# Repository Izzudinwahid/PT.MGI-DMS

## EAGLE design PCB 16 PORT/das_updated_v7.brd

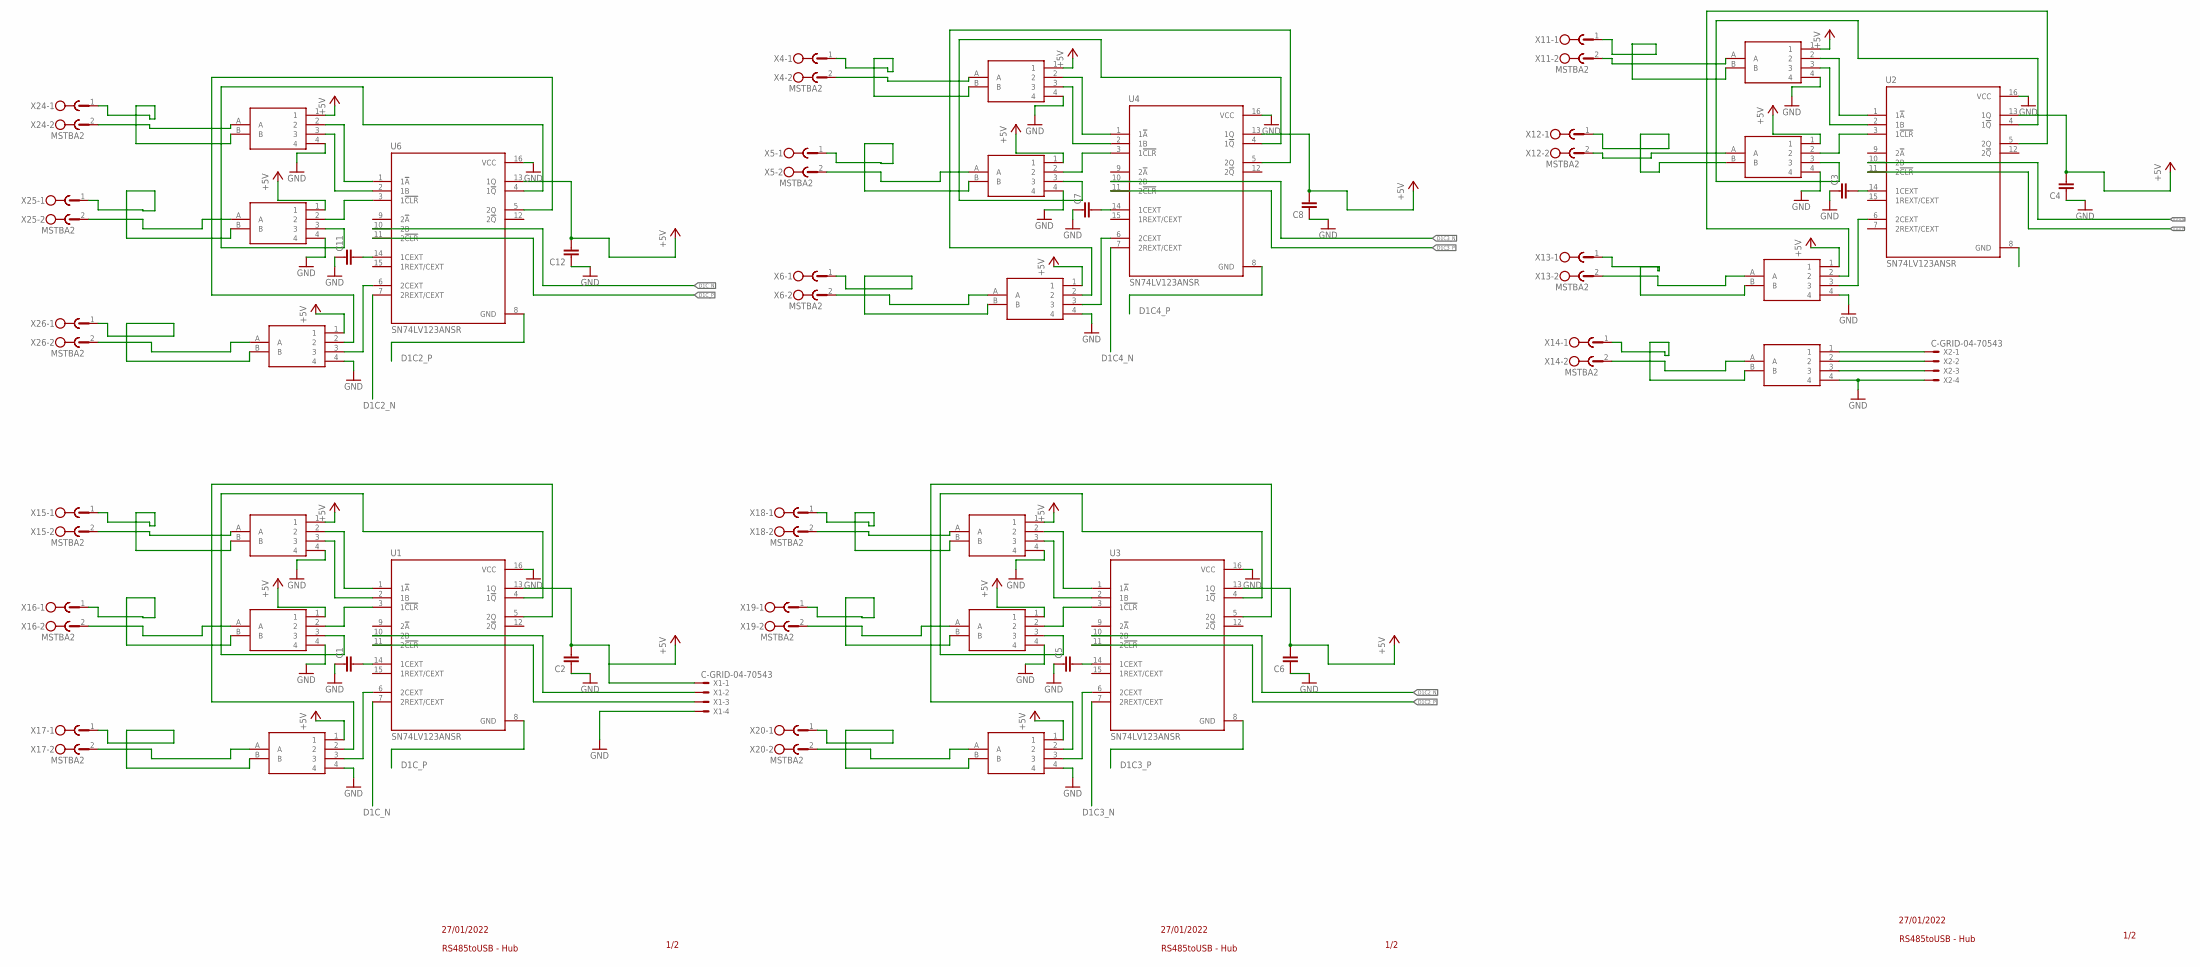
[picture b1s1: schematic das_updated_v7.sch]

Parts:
C1, C2, C3, C4, C5, C6, C7, C8, C11, C12: C-EUC0603K; C0603K
U1, U2, U3, U4, U6: SN74LV123ANSR; SOIC127P780X200-16N
USB2RS1, USB2RS2, USB2RS3, USB2RS4, USB2RS5, USB2RS6, USB2RS7, USB2RS8, USB2RS9, USB2RS10, USB2RS11, USB2RS12, USB2RS13, USB2RS17, USB2RS18, USB2RS19: USB2RS485
X1, X2: C-GRID-04-70543; 70543-04
X4, X5, X6, X11, X12, X13, X14, X15, X16, X17, X18, X19, X20, X24, X25, X26: MSTBA2

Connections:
+5V: C2.2, C4.2, C6.2, C8.2, C12.2, U1.13 (1Q), U2.13 (1Q), U3.13 (1Q), U4.13 (1Q), U6.13 (1Q), USB2RS1.1, USB2RS2.1, USB2RS3.1, USB2RS4.1, USB2RS5.1, USB2RS6.1, USB2RS7.1, USB2RS9.1, USB2RS10.1, USB2RS11.1, USB2RS12.1, USB2RS13.1, USB2RS17.1, USB2RS18.1, USB2RS19.1, X1.1
D1C2_N: U3.10 (2B), U6.7 (2REXT/CEXT)
D1C2_P: U3.11 (2!CLR), U6.8 (GND)
D1C3_N: U3.7 (2REXT/CEXT), U4.10 (2B)
D1C3_P: U3.8 (GND), U4.11 (2!CLR)
D1C4_N: U2.10 (2B), U4.7 (2REXT/CEXT)
D1C4_P: U2.11 (2!CLR), U4.8 (GND)
D1C_N: U1.7 (2REXT/CEXT), U6.10 (2B)
D1C_P: U1.8 (GND), U6.11 (2!CLR)
D2-: USB2RS8.2, X2.2
D_N: U1.11 (2!CLR), X1.3
D_P: U1.10 (2B), X1.2
GND: C1.1, C2.1, C3.1, C4.1, C5.1, C6.1, C7.1, C8.1, C11.1, C12.1, U1.16 (VCC), U2.16 (VCC), U3.16 (VCC), U4.16 (VCC), U6.16 (VCC), USB2RS1.4, USB2RS2.4, USB2RS3.4, USB2RS4.4, USB2RS5.4, USB2RS6.4, USB2RS7.4, USB2RS8.4, USB2RS9.4, USB2RS10.4, USB2RS11.4, USB2RS12.4, USB2RS13.4, USB2RS17.4, USB2RS18.4, USB2RS19.4, X1.4, X2.4
MOD2_N: U1.6 (2CEXT), USB2RS3.3
MOD2_N1: U3.6 (2CEXT), USB2RS10.3
MOD2_N2: U4.6 (2CEXT), USB2RS13.3
MOD2_N4: U6.6 (2CEXT), USB2RS19.3
MOD2_P: U1.5 (2Q), USB2RS3.2
MOD2_P1: U3.5 (2Q), USB2RS10.2
MOD2_P2: U4.5 (2Q), USB2RS13.2
MOD2_P4: U6.5 (2Q), USB2RS19.2
MOD3_N: U1.4 (1!Q), USB2RS2.3
MOD3_N1: U3.4 (1!Q), USB2RS9.3
MOD3_N2: U4.4 (1!Q), USB2RS12.3
MOD3_N4: U6.4 (1!Q), USB2RS18.3
MOD3_P: U1.3 (1!CLR), USB2RS2.2
MOD3_P1: U3.3 (1!CLR), USB2RS9.2
MOD3_P2: U4.3 (1!CLR), USB2RS12.2
MOD3_P4: U6.3 (1!CLR), USB2RS18.2
MOD4_N: U1.2 (1B), USB2RS1.3
MOD4_N1: U3.2 (1B), USB2RS4.3
MOD4_N2: U4.2 (1B), USB2RS11.3
MOD4_N4: U6.2 (1B), USB2RS17.3
MOD4_P: U1.1 (1!A), USB2RS1.2
MOD4_P1: U3.1 (1!A), USB2RS4.2
MOD4_P2: U4.1 (1!A), USB2RS11.2
MOD4_P4: U6.1 (1!A), USB2RS17.2
MOD7_N: U2.6 (2CEXT), USB2RS7.3
MOD7_P: U2.5 (2Q), USB2RS7.2
MOD8_N: U2.4 (1!Q), USB2RS6.3
MOD8_P: U2.3 (1!CLR), USB2RS6.2
MOD9_N: U2.2 (1B), USB2RS5.3
MOD9_P: U2.1 (1!A), USB2RS5.2
unnamed: C5.2, U3.14 (1CEXT)
unnamed: C7.2, U4.14 (1CEXT)
unnamed: USB2RS8.3, X2.3
unnamed: C11.2, U6.14 (1CEXT)
unnamed: C1.2, U1.14 (1CEXT)
unnamed: USB2RS8.1, X2.1
unnamed: C3.2, U2.14 (1CEXT)
X2_N: USB2RS3.B, X17.1
X2_N1: USB2RS10.B, X20.1
X2_N2: USB2RS13.B, X6.1
X2_N4: USB2RS19.B, X26.1
X2_P: USB2RS3.A, X17.2
X2_P1: USB2RS10.A, X20.2
X2_P2: USB2RS13.A, X6.2
X2_P4: USB2RS19.A, X26.2
X3_N: USB2RS2.B, X16.1
X3_N1: USB2RS9.B, X19.1
X3_N2: USB2RS12.B, X5.1
X3_N4: USB2RS18.B, X25.1
X3_P: USB2RS2.A, X16.2
X3_P1: USB2RS9.A, X19.2
X3_P2: USB2RS12.A, X5.2
X3_P4: USB2RS18.A, X25.2
X4_N: USB2RS1.B, X15.1
X4_N1: USB2RS4.B, X18.1
X4_N2: USB2RS11.B, X4.1
X4_N4: USB2RS17.B, X24.1
X4_P: USB2RS1.A, X15.2
X4_P1: USB2RS4.A, X18.2
X4_P2: USB2RS11.A, X4.2
X4_P4: USB2RS17.A, X24.2
X5_N: USB2RS8.B, X14.1
X5_P: USB2RS8.A, X14.2
X6_N: USB2RS7.B, X13.1
X6_P: USB2RS7.A, X13.2
X7_N: USB2RS6.B, X12.1
X7_P: USB2RS6.A, X12.2
X8_N: USB2RS5.B, X11.1
X8_P: USB2RS5.A, X11.2

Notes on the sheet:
27/01/2022
RS485toUSB - Hub
1/2

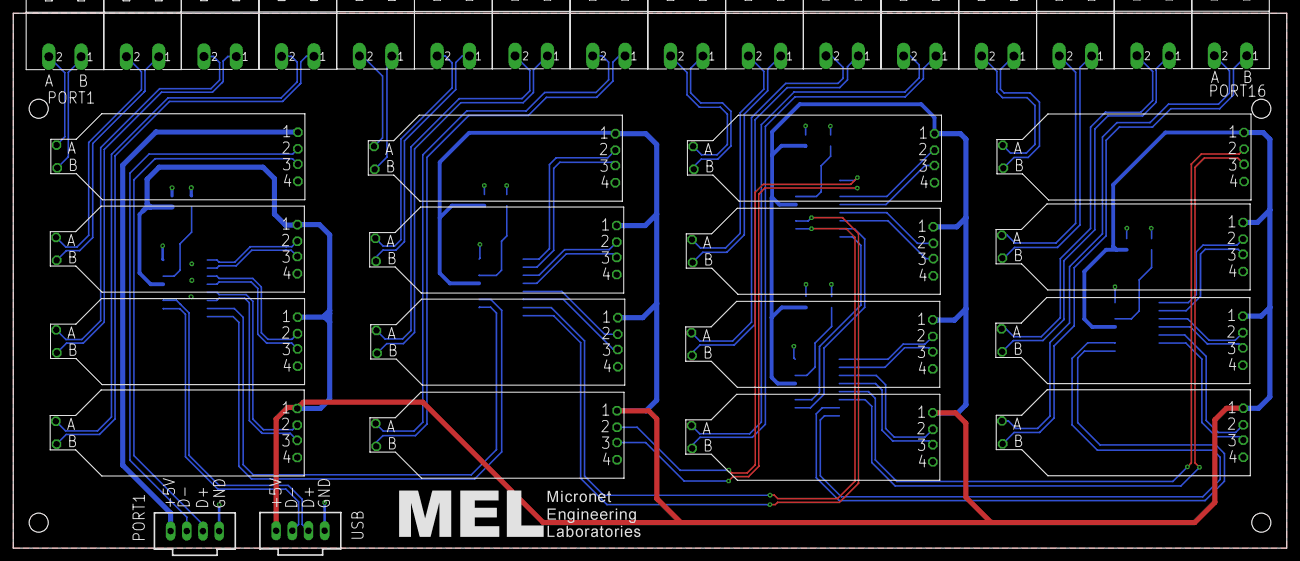
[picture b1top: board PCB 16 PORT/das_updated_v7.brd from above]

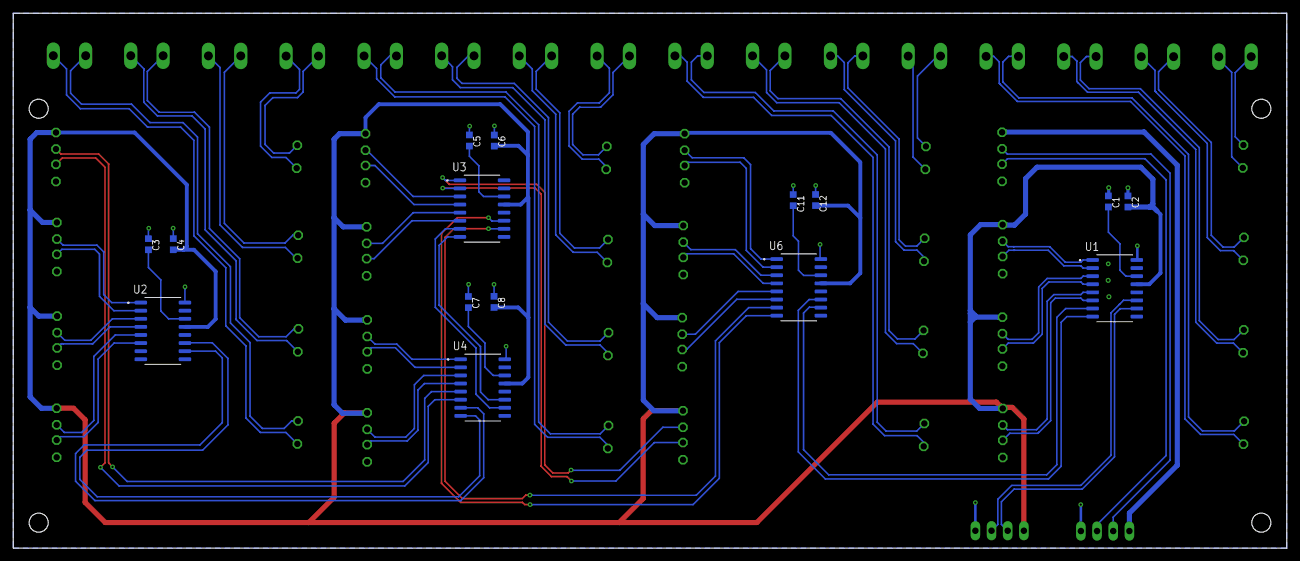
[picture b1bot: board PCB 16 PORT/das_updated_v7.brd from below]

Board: 2 copper layers, 200.0 x 84.0 mm, 49 parts (15 on the bottom side), 82 nets.

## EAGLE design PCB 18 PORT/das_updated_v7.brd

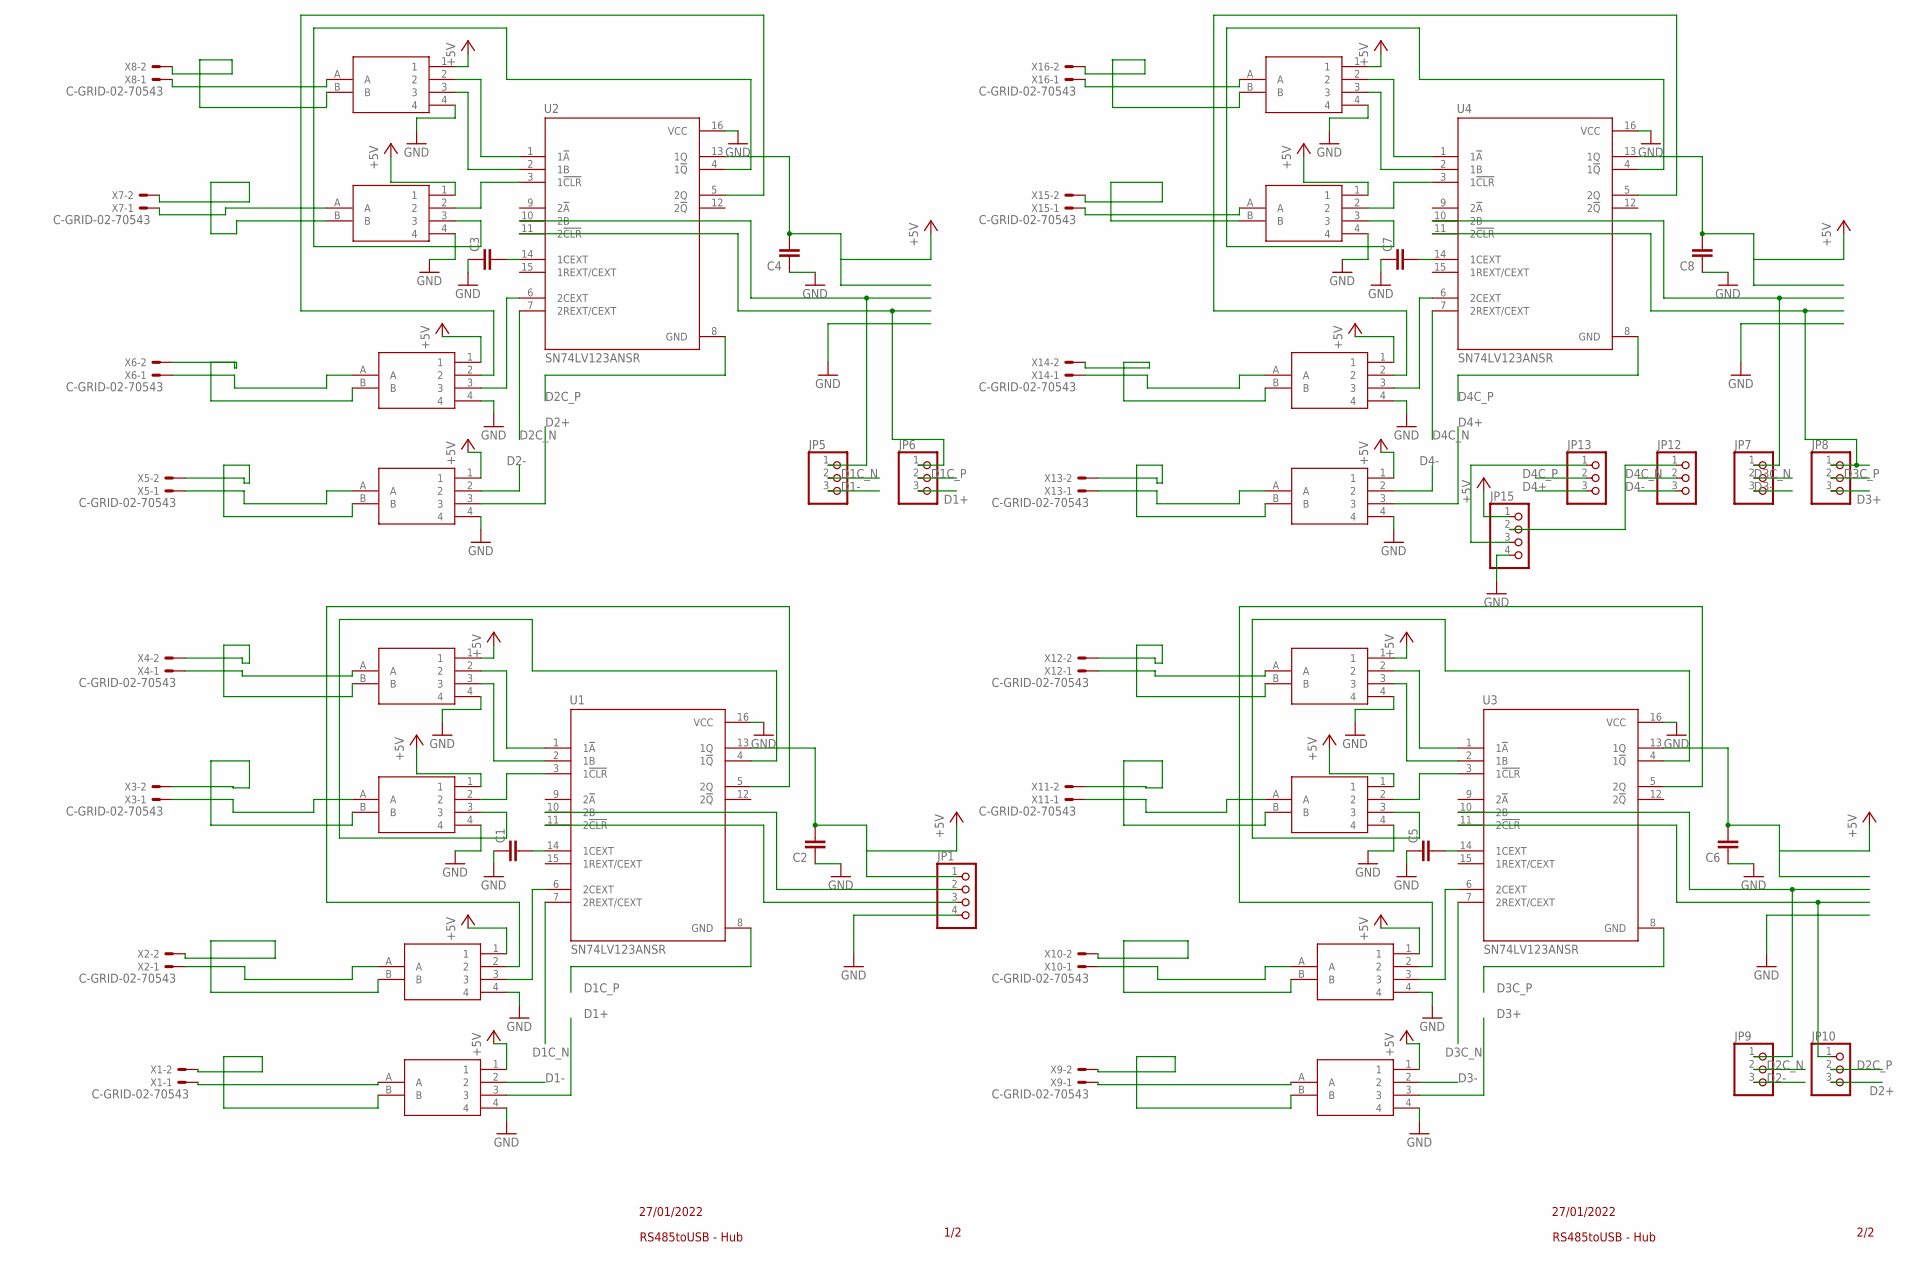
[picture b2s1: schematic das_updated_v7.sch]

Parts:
C1, C2, C3, C4, C5, C6, C7, C8: C-EUC0603K; C0603K
JP1, JP15: PINHD-1X4; 1X04
JP5, JP6, JP7, JP8, JP9, JP10, JP12, JP13: PINHD-1X3; 1X03
U1, U2, U3, U4: SN74LV123ANSR; SOIC127P780X200-16N
USB2RS1, USB2RS2, USB2RS3, USB2RS4, USB2RS5, USB2RS6, USB2RS7, USB2RS8, USB2RS9, USB2RS10, USB2RS11, USB2RS12, USB2RS13, USB2RS14, USB2RS15, USB2RS16: USB2RS485
X1, X2, X3, X4, X5, X6, X7, X8, X9, X10, X11, X12, X13, X14, X15, X16: C-GRID-02-70543; 70543-02

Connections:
+5V: C2.2, C4.2, C6.2, C8.2, JP1.1, JP15.1, U1.13 (1Q), U2.13 (1Q), U3.13 (1Q), U4.13 (1Q), USB2RS1.1, USB2RS2.1, USB2RS3.1, USB2RS4.1, USB2RS5.1, USB2RS6.1, USB2RS7.1, USB2RS8.1, USB2RS9.1, USB2RS10.1, USB2RS11.1, USB2RS12.1, USB2RS13.1, USB2RS14.1, USB2RS15.1, USB2RS16.1
D1+: JP6.3, USB2RS4.3
D1-: JP5.3, USB2RS4.2
D1C_N: JP5.2, U1.7 (2REXT/CEXT)
D1C_P: JP6.2, U1.8 (GND)
D2+: JP10.3, USB2RS8.3
D2-: JP9.3, USB2RS8.2
D2C_N: JP9.2, U2.7 (2REXT/CEXT)
D2C_P: JP10.2, U2.8 (GND)
D3+: JP8.3, USB2RS12.3
D3-: JP7.3, USB2RS12.2
D3C_N: JP7.2, U3.7 (2REXT/CEXT)
D3C_P: JP8.2, U3.8 (GND)
D4+: JP13.3, USB2RS16.3
D4-: JP12.3, USB2RS16.2
D4C_N: JP12.2, U4.7 (2REXT/CEXT)
D4C_P: JP13.2, U4.8 (GND)
D_N: JP1.3, U1.11 (2!CLR)
D_P: JP1.2, U1.10 (2B)
GND: C1.1, C2.1, C3.1, C4.1, C5.1, C6.1, C7.1, C8.1, JP1.4, JP15.4, U1.16 (VCC), U2.16 (VCC), U3.16 (VCC), U4.16 (VCC), USB2RS1.4, USB2RS2.4, USB2RS3.4, USB2RS4.4, USB2RS5.4, USB2RS6.4, USB2RS7.4, USB2RS8.4, USB2RS9.4, USB2RS10.4, USB2RS11.4, USB2RS12.4, USB2RS13.4, USB2RS14.4, USB2RS15.4, USB2RS16.4
MOD2_N: U1.6 (2CEXT), USB2RS3.3
MOD2_P: U1.5 (2Q), USB2RS3.2
MOD3_N: U1.4 (1!Q), USB2RS2.3
MOD3_P: U1.3 (1!CLR), USB2RS2.2
MOD4_N: U1.2 (1B), USB2RS1.3
MOD4_P: U1.1 (1!A), USB2RS1.2
MOD7_N: U2.6 (2CEXT), USB2RS7.3
MOD7_P: U2.5 (2Q), USB2RS7.2
MOD8_N: U2.4 (1!Q), USB2RS6.3
MOD8_P: U2.3 (1!CLR), USB2RS6.2
MOD9_N: U2.2 (1B), USB2RS5.3
MOD9_P: U2.1 (1!A), USB2RS5.2
MOD10_N: U3.6 (2CEXT), USB2RS11.3
MOD10_P: U3.5 (2Q), USB2RS11.2
MOD11_N: U3.4 (1!Q), USB2RS10.3
MOD11_P: U3.3 (1!CLR), USB2RS10.2
MOD12_N: U3.2 (1B), USB2RS9.3
MOD12_P: U3.1 (1!A), USB2RS9.2
MOD14_N: U4.6 (2CEXT), USB2RS15.3
MOD14_P: U4.5 (2Q), USB2RS15.2
MOD15_N: U4.4 (1!Q), USB2RS14.3
MOD15_P: U4.3 (1!CLR), USB2RS14.2
MOD16_N: U4.2 (1B), USB2RS13.3
MOD16_P: U4.1 (1!A), USB2RS13.2
unnamed: JP6.1, U2.11 (2!CLR)
unnamed: C1.2, U1.14 (1CEXT)
unnamed: C3.2, U2.14 (1CEXT)
unnamed: JP5.1, U2.10 (2B)
unnamed: JP12.1, JP15.2
unnamed: JP13.1, JP15.3
unnamed: C5.2, U3.14 (1CEXT)
unnamed: C7.2, U4.14 (1CEXT)
unnamed: JP7.1, U4.10 (2B)
unnamed: JP8.1, U4.11 (2!CLR)
unnamed: JP9.1, U3.10 (2B)
unnamed: JP10.1, U3.11 (2!CLR)
X1_N: USB2RS4.B, X1.2
X1_P: USB2RS4.A, X1.1
X2_N: USB2RS3.B, X2.2
X2_P: USB2RS3.A, X2.1
X3_N: USB2RS2.B, X3.2
X3_P: USB2RS2.A, X3.1
X4_N: USB2RS1.B, X4.2
X4_P: USB2RS1.A, X4.1
X5_N: USB2RS8.B, X5.2
X5_P: USB2RS8.A, X5.1
X6_N: USB2RS7.B, X6.2
X6_P: USB2RS7.A, X6.1
X7_N: USB2RS6.B, X7.2
X7_P: USB2RS6.A, X7.1
X8_N: USB2RS5.B, X8.2
X8_P: USB2RS5.A, X8.1
X9_N: USB2RS12.B, X9.2
X9_P: USB2RS12.A, X9.1
X10_N: USB2RS11.B, X10.2
X10_P: USB2RS11.A, X10.1
X11_N: USB2RS10.B, X11.2
X11_P: USB2RS10.A, X11.1
X12_N: USB2RS9.B, X12.2
X12_P: USB2RS9.A, X12.1
X13_N: USB2RS16.B, X13.2
X13_P: USB2RS16.A, X13.1
X14_N: USB2RS15.B, X14.2
X14_P: USB2RS15.A, X14.1
X15_N: USB2RS14.B, X15.2
X15_P: USB2RS14.A, X15.1
X16_N: USB2RS13.B, X16.2
X16_P: USB2RS13.A, X16.1

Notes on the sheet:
27/01/2022
RS485toUSB - Hub
2/2
1/2

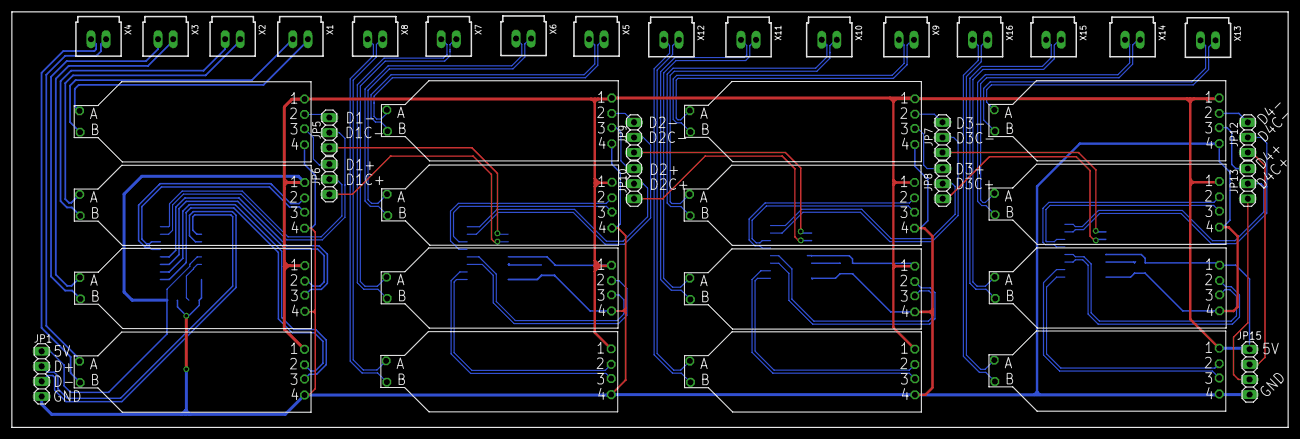
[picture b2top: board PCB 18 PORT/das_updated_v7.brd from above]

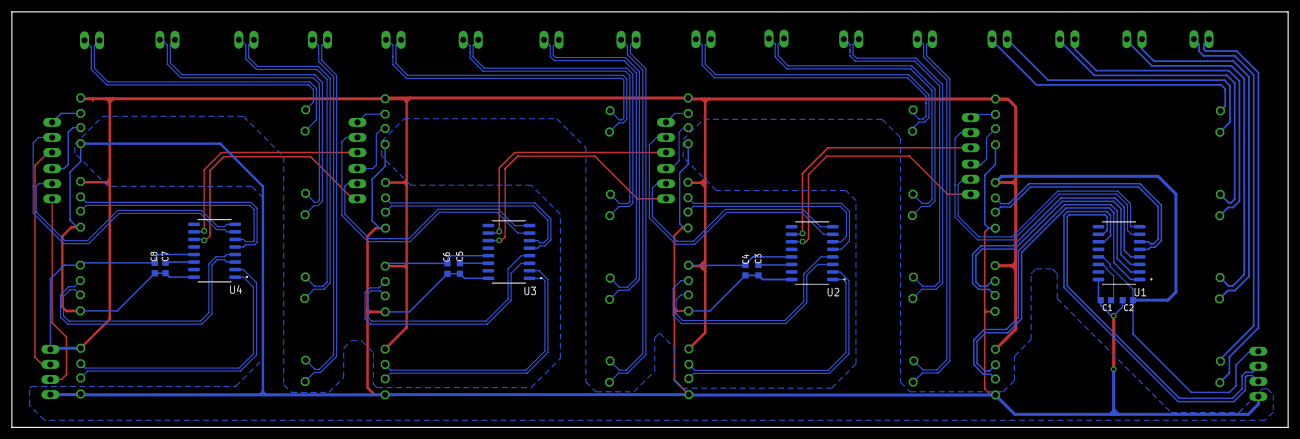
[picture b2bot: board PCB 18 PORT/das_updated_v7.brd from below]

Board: 2 copper layers, 215.0 x 70.0 mm, 54 parts (12 on the bottom side), 88 nets.

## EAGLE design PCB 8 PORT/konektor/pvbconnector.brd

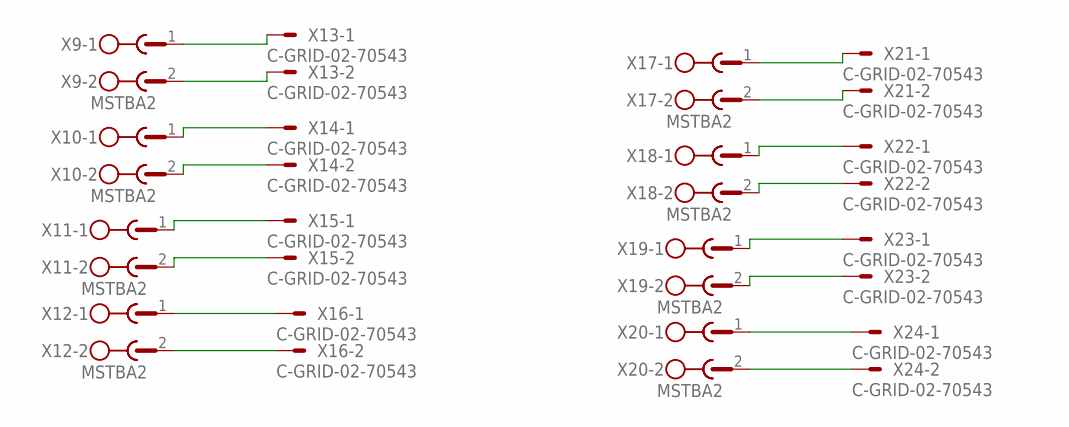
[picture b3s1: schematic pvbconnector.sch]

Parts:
X9, X10, X11, X12, X17, X18, X19, X20: MSTBA2
X13, X14, X15, X16, X21, X22, X23, X24: C-GRID-02-70543; 70543-02

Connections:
unnamed: X9.1, X13.1
unnamed: X9.2, X13.2
unnamed: X10.1, X14.1
unnamed: X10.2, X14.2
unnamed: X11.1, X15.1
unnamed: X11.2, X15.2
unnamed: X12.1, X16.1
unnamed: X12.2, X16.2
unnamed: X17.1, X21.1
unnamed: X17.2, X21.2
unnamed: X18.1, X22.1
unnamed: X18.2, X22.2
unnamed: X19.1, X23.1
unnamed: X19.2, X23.2
unnamed: X20.1, X24.1
unnamed: X20.2, X24.2

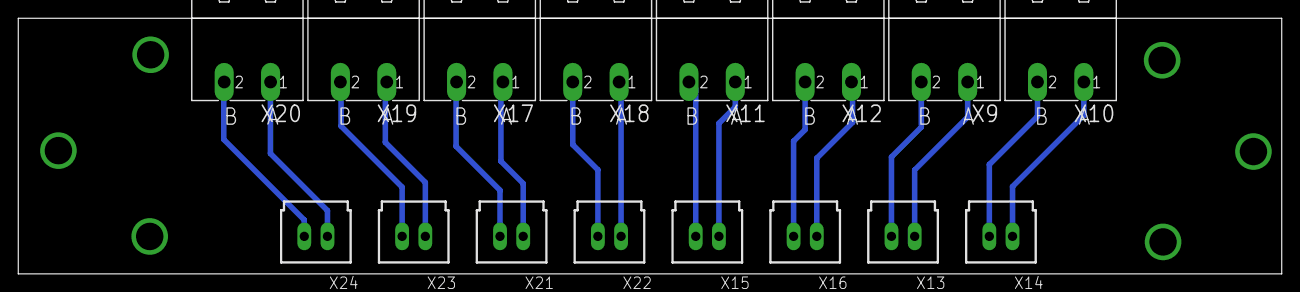
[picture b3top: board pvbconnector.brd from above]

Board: 2 copper layers, 138.4 x 28.0 mm, 16 parts (0 on the bottom side), 16 nets.

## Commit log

2022-08-10 DMS V1.2
    Micom P122, P123, P141, P143, P442,P443
2022-08-10 menambahkan gambar DMS
2024-03-12 tambahan PCB
2024-07-08 PCB 16 PORT
